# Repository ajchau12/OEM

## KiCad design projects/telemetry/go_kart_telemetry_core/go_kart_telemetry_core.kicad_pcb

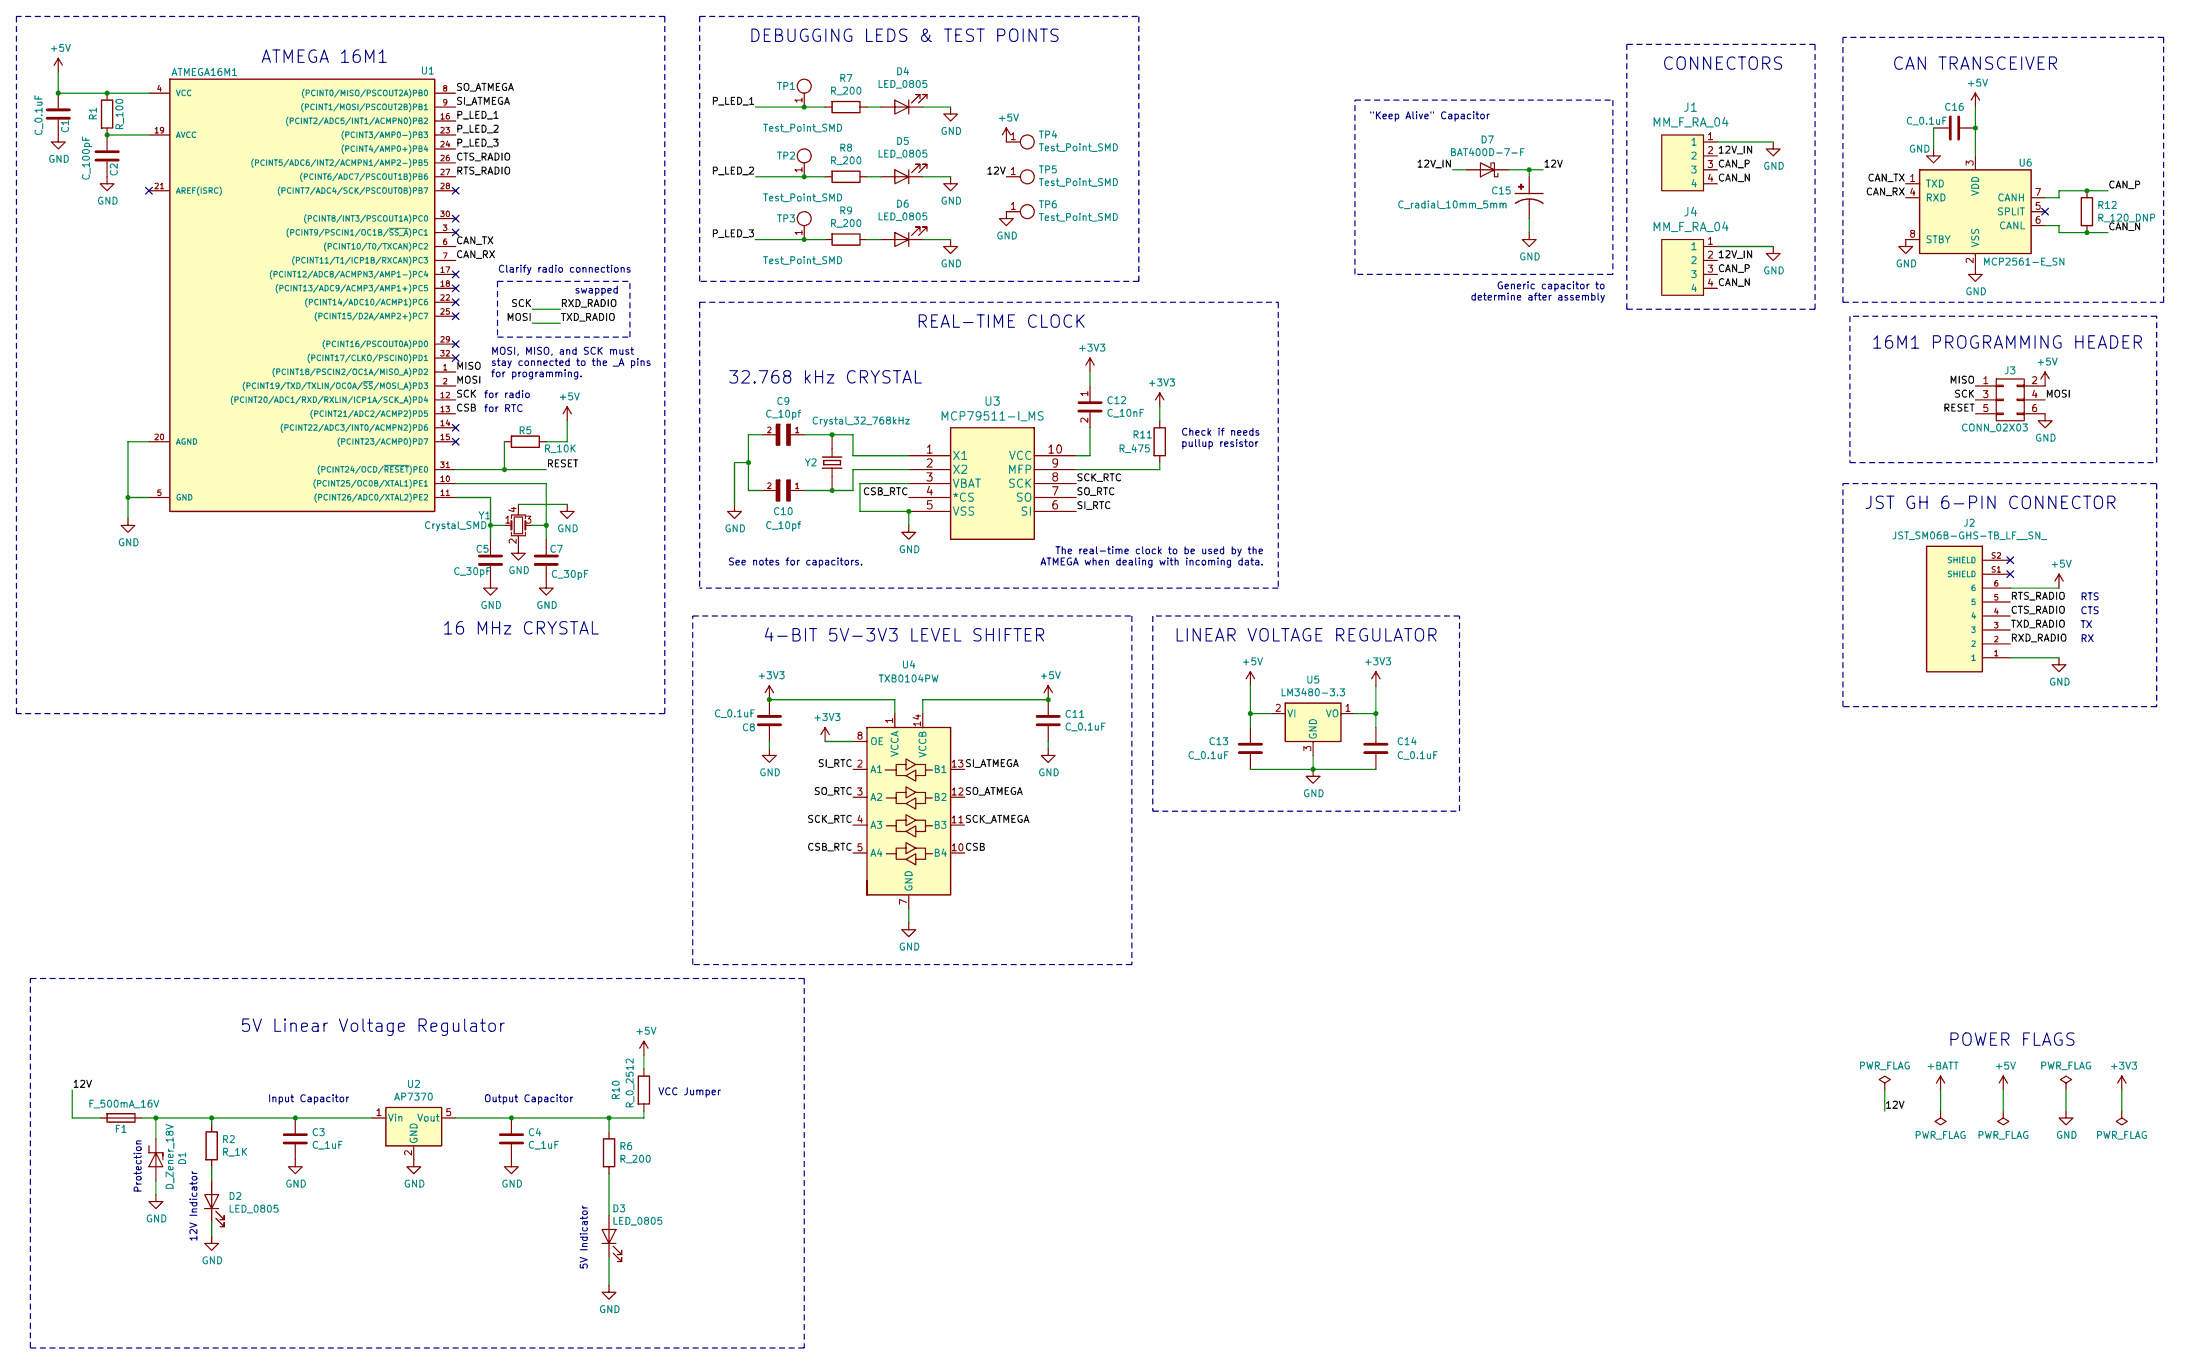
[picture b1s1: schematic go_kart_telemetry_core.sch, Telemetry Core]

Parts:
C1, C8, C11, C13, C14, C16: C_0.1uF; C_0805_OEM; MPN 478-3352-1-ND
C2: C_100pF; C_0805_OEM; MPN 732-7852-1-ND
C3, C4: C_1uF; C_0805_OEM
C5, C7: C_30pF; C_0805_OEM; MPN 1276-1130-1-ND
C9, C10: C_10pf
C12: C_10nF; C_1206_OEM; MPN C1206C103KCRACTU
C15: C_radial_10mm_5mm; PARTREV 28-FEB-20
D1: D_Zener_18V; DO-214AA; MPN SMBJ5355B-TPMSCT-ND
D2, D3, D4, D5, D6: LED_0805; LED_0805_OEM; MPN 475-1410-1-ND
D7: BAT400D-7-F; SOT-23-3_OEM
F1: F_500mA_16V; Fuse_1210; MPN 507-1786-1-ND
J1, J4: MM_F_RA_04; micromatch_female_ra_4; MPN 338070-4
J2: JST_SM06B-GHS-TB_LF__SN_; PARTREV N/A
J3: CONN_02X03; Pin_Header_Straight_2x03; MPN 609-3234-ND
R1: R_100; R_0805_OEM; MPN RNCP0805FTD100RCT-ND
R2: R_1K; R_0805_OEM; MPN RNCP0805FTD1K00CT-ND
R5: R_10K; R_0805_OEM; MPN CRS0805-FX-1002ELFCT-ND
R6, R7, R8, R9: R_200; R_0805_OEM; MPN RMCF0805JT200RCT-ND
R10: R_0_2512; R_2512_OEM; MPN A121322CT-ND
R11: R_475; R_0805_OEM; MPN 311-475CRCT-ND
R12: R_120_DNP; R_0805_OEM; MPN 667-ERJ-6ENF1200V
TP1, TP2, TP3, TP4, TP5, TP6: Test_Point_SMD
U1: ATMEGA16M1; TQFP-32_7x7mm_Pitch0.8mm; MPN ATMEGA16M1-AU-ND
U2: AP7370; SOT-23-5; MPN AP7370-50W5-7DICT-ND
U3: MCP79511-I_MS; MCP79511_I_MS
U4: TXB0104PW; TSSOP-14_4.4x5mm_P0.65mm
U5: LM3480-3.3; SOT-23
U6: MCP2561-E_SN; SOIC-8_3.9x4.9mm_Pitch1.27mm_OEM; MPN MCP2561-E/SN-ND
Y1: Crystal_SMD; Crystal_SMD_FA238; MPN 887-1125-1-ND
Y2: Crystal_32_768kHz; Crystal_32_768kHZ

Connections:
+3V3: C8.2, C12.1, C14.1, R11.1, U4.1 (VCCA), U4.8 (OE), U5.1 (VO)
+5V: C1.1, C11.1, C13.1, C16.1, J2.6, J3.2, R1.1, R5.1, R10.1, TP4.1, U1.4 (VCC), U4.14 (VCCB), U5.2 (VI), U6.3 (VDD)
/12V: C15.P, D7.1 (K), F1.2, TP5.1
/12V_IN: D7.2 (A), J1.2, J4.2
/CAN_N: J1.4, J4.4, R12.2, U6.6 (CANL)
/CAN_P: J1.3, J4.3, R12.1, U6.7 (CANH)
/CAN_RX: U1.7 ((PCINT11/T1/ICP1B/RXCAN)PC3), U6.4 (RXD)
/CAN_TX: U1.6 ((PCINT10/T0/TXCAN)PC2), U6.1 (TXD)
/CSB: U1.13 ((PCINT21/ADC2/ACMP2)PD5), U4.10 (B4)
/CSB_RTC: U3.4 (*CS), U4.5 (A4)
/CTS_RADIO: J2.4, U1.26 ((PCINT5/ADC6/INT2/ACMPN1/AMP2-)PB5)
/MISO: J3.1, U1.1 ((PCINT18/PSCIN2/OC1A/MISO_A)PD2)
/MOSI: J2.3, J3.4, U1.2 ((PCINT19/TXD/TXLIN/OC0A/~SS~/MOSI_A)PD3)
/P_LED_1: R7.2, TP1.1, U1.16 ((PCINT2/ADC5/INT1/ACMPN0)PB2)
/P_LED_2: R8.2, TP2.1, U1.23 ((PCINT3/AMP0-)PB3)
/P_LED_3: R9.2, TP3.1, U1.24 ((PCINT4/AMP0+)PB4)
/RESET: J3.5, R5.2, U1.31 ((PCINT24/OCD/~RESET~)PE0)
/RTS_RADIO: J2.5, U1.27 ((PCINT6/ADC7/PSCOUT1B)PB6)
/RXD_RADIO: J2.2, J3.3, U1.12 ((PCINT20/ADC1/RXD/RXLIN/ICP1A/SCK_A)PD4)
/SCK_ATMEGA: U4.11 (B3)
/SCK_RTC: U3.8 (SCK), U4.4 (A3)
/SI_ATMEGA: U1.9 ((PCINT1/MOSI/PSCOUT2B)PB1), U4.13 (B1)
/SI_RTC: U3.6 (SI), U4.2 (A1)
/SO_ATMEGA: U1.8 ((PCINT0/MISO/PSCOUT2A)PB0), U4.12 (B2)
/SO_RTC: U3.7 (SO), U4.3 (A2)
GND: C1.2, C2.2, C3.2, C4.2, C5.2, C7.2, C8.1, C9.2, C10.2, C11.2, C13.2, C14.2, C15.N, C16.2, D1.2 (A), D2.1 (K), D3.1 (K), D4.1 (K), D5.1 (K), D6.1 (K), J1.1, J2.1, J3.6, J4.1, TP6.1, U1.5 (GND), U1.20 (AGND), U2.2 (GND), U3.3 (VBAT), U3.5 (VSS), U4.7 (GND), U5.3 (GND), U6.2 (VSS), U6.8 (STBY), Y1.2, Y1.4
unnamed: C2.1, R1.2, U1.19 (AVCC)
unnamed: C3.1, D1.1 (K), F1.1, R2.1, U2.1 (Vin)
unnamed: C4.1, R6.1, R10.2, U2.5 (Vout)
unnamed: C5.1, U1.11 ((PCINT26/ADC0/XTAL2)PE2), Y1.1
unnamed: C7.1, U1.10 ((PCINT25/OC0B/XTAL1)PE1), Y1.3
unnamed: C9.1, U3.1 (X1), Y2.1
unnamed: C10.1, U3.2 (X2), Y2.2
unnamed: C12.2, U3.10 (VCC)
unnamed: D2.2 (A), R2.2
unnamed: D3.2 (A), R6.2
unnamed: D4.2 (A), R7.1
unnamed: D5.2 (A), R8.1
unnamed: D6.2 (A), R9.1
unnamed: R11.2, U3.9 (MFP)

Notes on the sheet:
12V Indicator
Protection
5V Linear Voltage Regulator
VCC Jumper
5V Indicator
CAN TRANSCEIVER
ATMEGA 16M1
16 MHz CRYSTAL
POWER FLAGS
16M1 PROGRAMMING HEADER
CONNECTORS
DEBUGGING LEDS & TEST POINTS
JST GH 6-PIN CONNECTOR
RTS
CTS
MOSI, MISO, and SCK must stay connected to the _A pins for programming.
LINEAR VOLTAGE REGULATOR
4-BIT 5V-3V3 LEVEL SHIFTER
REAL-TIME CLOCK
"Keep Alive" Capacitor
Clarify radio connections
Generic capacitor to determine after assembly
swapped
for RTC
Check if needs pullup resistor
for radio
See notes for capacitors.
The real-time clock to be used by the ATMEGA when dealing with incoming data.
32.768 kHz CRYSTAL
Input Capacitor
Output Capacitor

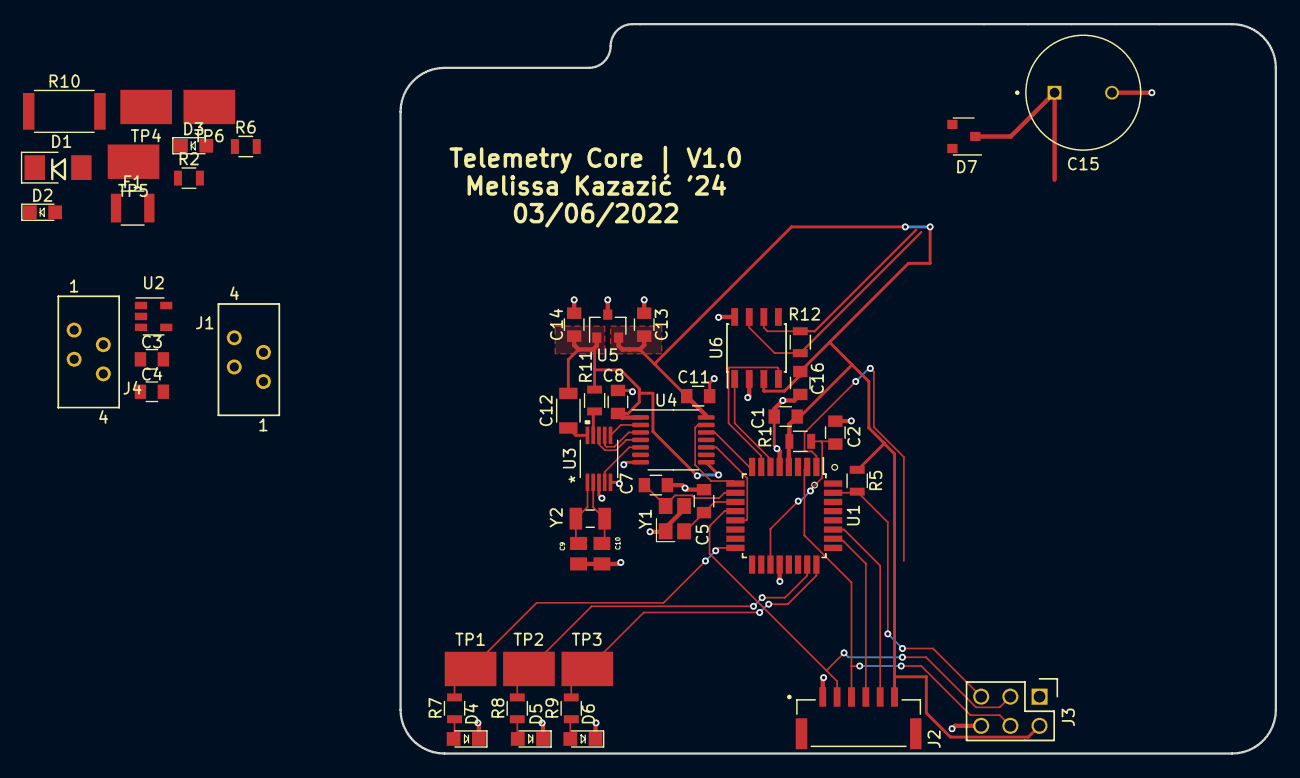
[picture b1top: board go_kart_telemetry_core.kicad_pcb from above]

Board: 2 copper layers, 76.2 x 63.5 mm, 51 parts (0 on the bottom side), 39 nets.

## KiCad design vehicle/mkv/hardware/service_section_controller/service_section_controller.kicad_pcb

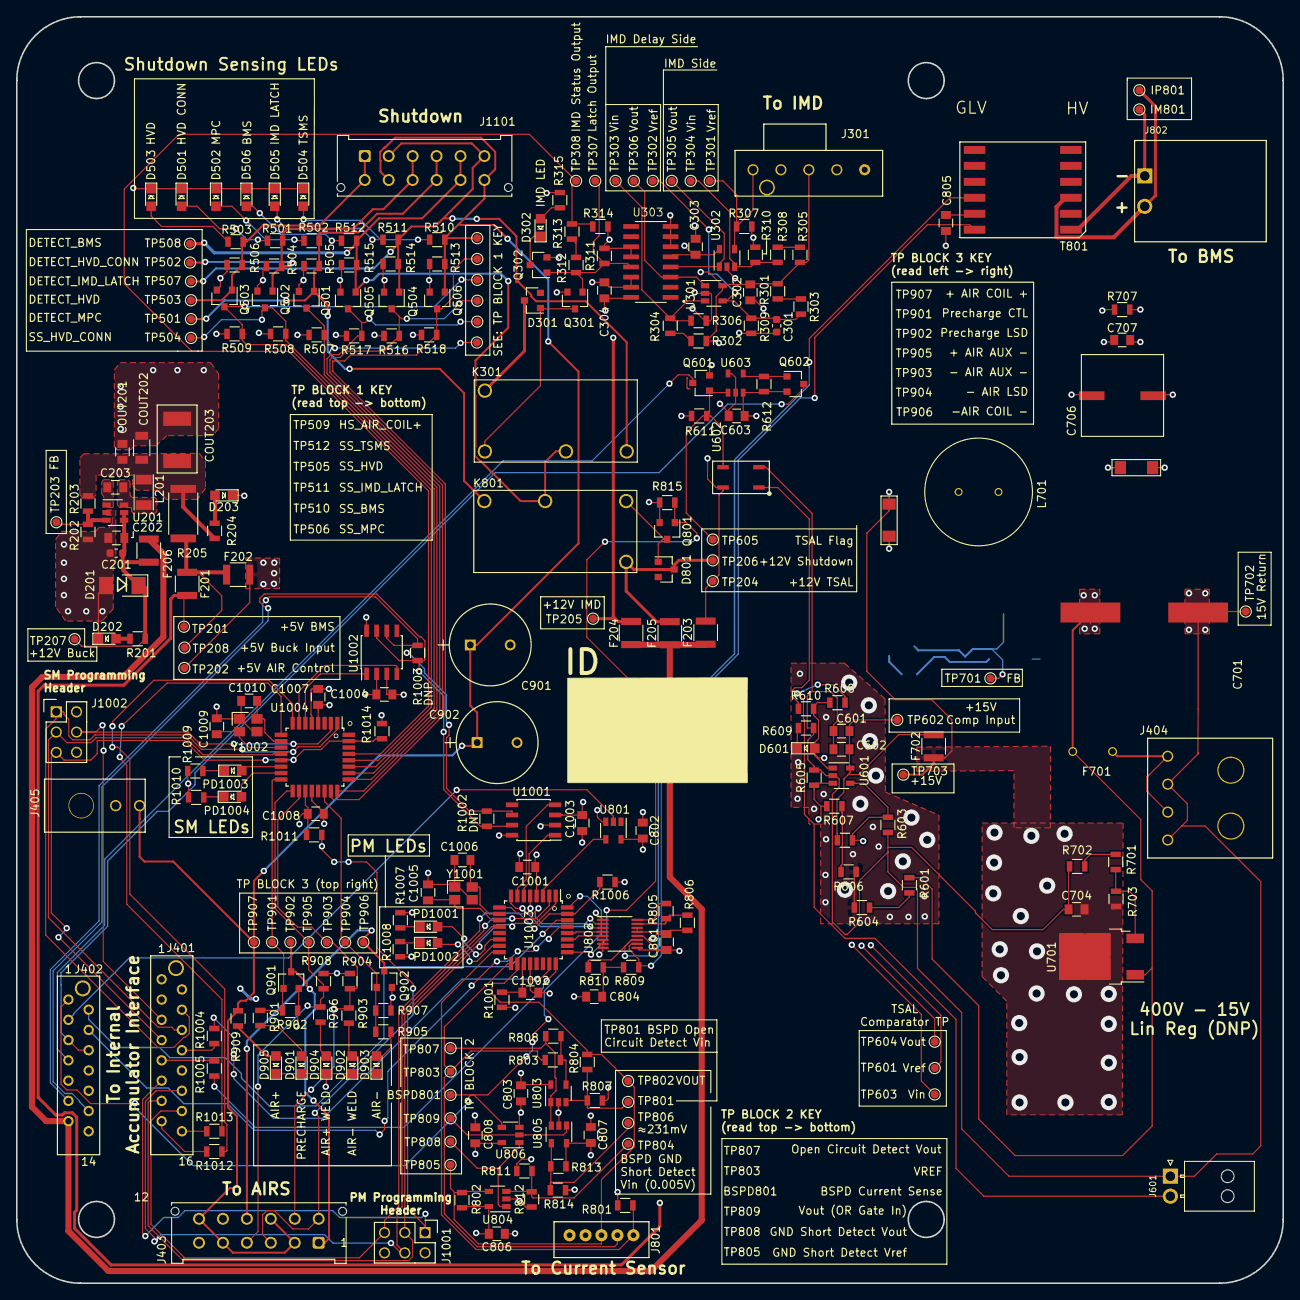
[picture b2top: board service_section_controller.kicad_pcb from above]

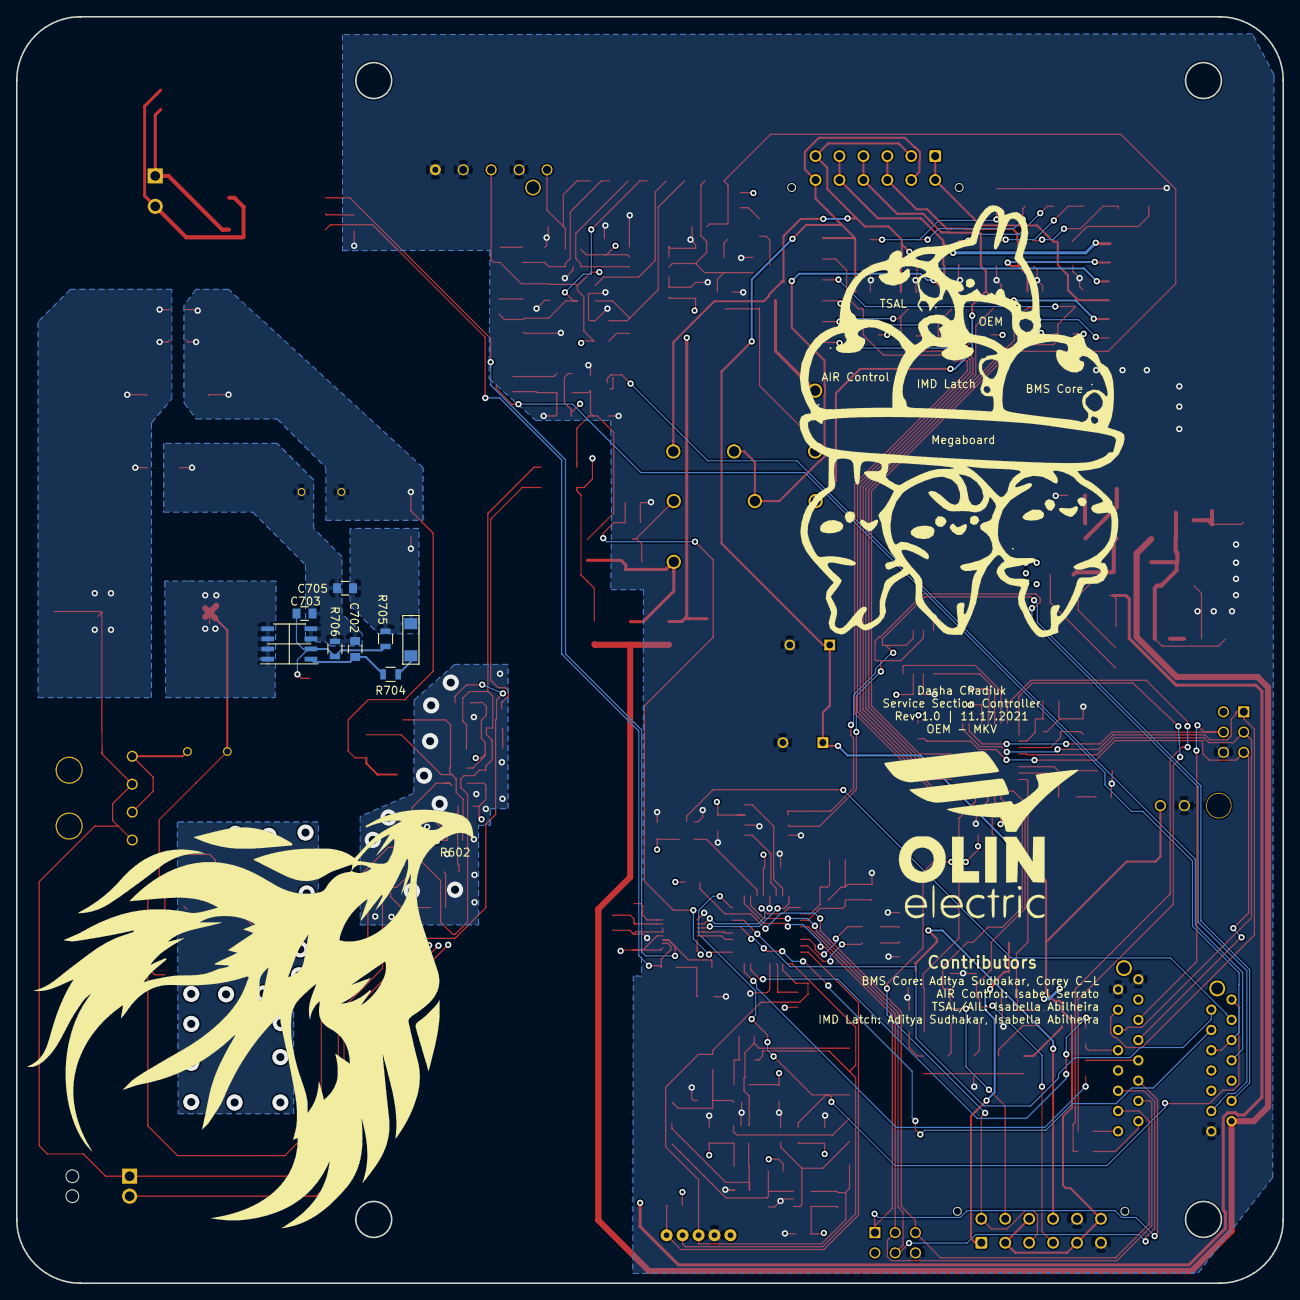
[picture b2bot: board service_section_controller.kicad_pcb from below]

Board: 4 copper layers, 158.8 x 158.8 mm, 274 parts (8 on the bottom side), 149 nets.

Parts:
BSPD801: Test_Point_SMD; TestPoint_Pad_D1.0mm
C201, C301: C_2.2uF; C_0603_1608Metric
C202, C203, C302, C303, C304, C602, C801, C802, C803, C806, C807, C808, C1001, C1003, C1004, C1007: C_0.1uF; C_0805_OEM
C601: C_10uF; C_0805_OEM
C603, C704, C707: C_1uF; C_0805_OEM
C701: C_10uF_450V
C702: C_2.2uF; C_0805_OEM
C703: C_470pF; C_0805_OEM
C705: C_.22uF; C_0805_OEM
C706: C_100uF+
C804, C805: C_10nF; C_0805_OEM
C901, C902: CP_1mF; C_Radial_D10_L13_P5_OEM
C1002, C1008: C_100pF; C_0805_OEM
C1005, C1006, C1009, C1010: C_30pF; C_0805_OEM
COUT201: C_47uF; C_0805_OEM
COUT202: C_22uF; C_1206_OEM
COUT203: C_33uF; Fuse_1812
D201: D_Zener_18V; DO-214AA
D202, D203, D302, D501, D502, D503, D504, D505, D506, D601, D901, D902, D903, D904, D905: LED_0805; LED_0805_OEM
D301, D801: BAS40-00; SOT-23
D701, D702, D703: Diode_600V_1A_SM
F201, F202, F203, F204, F205, F206, F702: 500mA; Fuse_1210
F701: F_21mA_420V
IM801: Test_Point_SMD; TestPoint_Pad_D1.0mm
IP801: Test_Point_SMD; TestPoint_Pad_D1.0mm
J301: UF_5_VT; Ultrafit_5
J401: MM_F_VT_16; micromatch_female_vert_16
J402: MM_F_VT_14; micromatch_female_vert_14
J403, J1101: MicroFit_VT_12
J404: Ultrafit_4_RA
J405: MicroFit_RA_V_2
J601: NanoFit_2; NanoFit_Molex_1x02x2.50mm_Angled_OEM
J801: B5B-PH-K-S
J802: isoSPI-Cutout; iso_spi_cutout
J1001, J1002: CONN_02X03; Pin_Header_Straight_2x03
K301, K801: G5Q-1A4-DC12; Relay_SPST_OMRON-G5Q-1A4_OEM
L201: L_100uH; L_100uH_OEM
L701: L_1.2mH
PD1001, PD1002, PD1003, PD1004: LED_0805; LED_0805_OEM
Q301, Q302, Q501, Q502, Q503, Q504, Q505, Q506, Q601, Q602, Q801, Q901, Q902: SSM3K333R; SOT-23F
R201, R301, R313, R315, R501, R502, R503, R510, R511, R512, R609, R805, R806, R812, R909: R_1K; R_0805_OEM
R202: R_25K; R_0805_OEM
R203, R504, R505, R506, R513, R514, R515: R_100K; R_0805_OEM
R204, R901, R903, R905, R906, R1004, R1005, R1007, R1008, R1009, R1010, R1012, R1013: R_200; R_0805_OEM
R205: R_0_2512; R_2512_OEM
R302, R305, R307, R312: R_2.2K; R_0805_OEM
R303: R_120K; R_0805_OEM
R304, R308: R_300K; R_0805_OEM
R306, R310, R311: R_604K; R_0805_OEM
R309: R_1.82M; R_0805_OEM
R314: R_1.13K; R_0805_OEM
R507, R508, R509, R516, R517, R518, R605, R611, R612, R704, R801, R802, R803, R804, R807, R808, R814, R815, R902, R904, R907, R908, R1006, R1014: R_10K; R_0805_OEM
R601, R604, R606, R607: R_270K; R_0805_OEM
R602: R_51.1K; R_0805_OEM
R603: R_1.91K; R_0805_OEM
R608: R_1.43K; R_0805_OEM
R610: R_499; R_0805_OEM
R701: R_43k; R_0805_OEM
R702, R705: R_23.7K; R_0805_OEM
R703: R_6.04K; R_0805_OEM
R706: R_4.99K; R_0805_OEM
R707: R_3K; R_0805_OEM
R809, R810: R_60.4; R_0805_OEM
R811: R_1M; R_0805_OEM
R813: R_475; R_0805_OEM
R1001, R1011: R_100; R_0805_OEM
R1002, R1003: R_120_DNP; R_0805_OEM
T801: T_LAN_SM91501ALE
TP201: 5V_BMS; TestPoint_Pad_D1.0mm
TP202: 5V_AIR_CONTROL; TestPoint_Pad_D1.0mm
TP203, TP701: FB; TestPoint_Pad_D1.0mm
TP204: 12V_TSAL; TestPoint_Pad_D1.0mm
TP205: 12V_IMD; TestPoint_Pad_D1.0mm
TP206: 12V_SHUTDOWN; TestPoint_Pad_D1.0mm
TP207: 12V_BUCK; TestPoint_Pad_D1.0mm
TP208: BUCK_OUTPUT; TestPoint_Pad_D1.0mm
TP301: IMD_OUTPUT; TestPoint_Pad_D1.0mm
TP302, TP303, TP306, TP307, TP801, TP804, TP805, TP806, TP807, TP808, TP809: Test_Point_SMD; TestPoint_Pad_D1.0mm
TP304: 8V_OPAMP; TestPoint_Pad_D1.0mm
TP305: OPAMP_OUTPUT; TestPoint_Pad_D1.0mm
TP308: IMD_STATUS_OUTPUT; TestPoint_Pad_D1.0mm
TP501: DETECT_MPC; TestPoint_Pad_D1.0mm
TP502: DETECT_HVD_CONN; TestPoint_Pad_D1.0mm
TP503: DETECT_HVD; TestPoint_Pad_D1.0mm
TP504: SS_HVD_CONN; TestPoint_Pad_D1.0mm
TP505: SS_HVD; TestPoint_Pad_D1.0mm
TP506: SS_MPC; TestPoint_Pad_D1.0mm
TP507: DETECT_IMD_LATCH; TestPoint_Pad_D1.0mm
TP508: DETECT_BMS; TestPoint_Pad_D1.0mm
TP509: DETECT_TSMS; TestPoint_Pad_D1.0mm
TP510: SS_BMS; TestPoint_Pad_D1.0mm
TP511: SS_IMD_LATCH; TestPoint_Pad_D1.0mm
TP512: SS_TSMS; TestPoint_Pad_D1.0mm
TP601: VIN; TestPoint_Pad_D1.0mm
TP602: 15V+; TestPoint_Pad_D1.0mm
TP603, TP803: VREF; TestPoint_Pad_D1.0mm
TP604: COMPARATOR_OUTPUT; TestPoint_Pad_D1.0mm
TP605: TSAL_FLAG; TestPoint_Pad_D1.0mm
TP702: 15V_RETURN; TestPoint_Pad_D1.0mm
TP703: 15V+_OUTPUT; TestPoint_Pad_D1.0mm
TP802: VOUT; TestPoint_Pad_D1.0mm
TP901: PRECHARGE_CTL; TestPoint_Pad_D1.0mm
TP902: PRECHARGE_LSD; TestPoint_Pad_D1.0mm
TP903: -AIR_WELD_DETECT; TestPoint_Pad_D1.0mm
TP904: -AIR_LSD; TestPoint_Pad_D1.0mm
TP905: +AIR_WELD_DETECT; TestPoint_Pad_D1.0mm
TP906: -AIR_COIL-; TestPoint_Pad_D1.0mm
TP907: +AIR_COIL+; TestPoint_Pad_D1.0mm
U201: TPS560430YF; SOT-23-6_OEM
U301, U302: TLV3701QDBVRG4Q1; SOT-23-5_OEM
U303: CD4044BDR; SOIC127P600X175-16N
U601: MCP6001; SOT-23-5
U602: CPC1025NTR; 4-pin_SOP
U603: BU4S11G2-TR; SSOP5
U701: LR8K4-G; TO-252-2
U702: MP9488; Converter_DCDC_MPS_MP9488
U801: SN74LVC1G17; SOT-23-5
U802: LTC6820HMS; MSOP-16_3x4mm_P0.5mm
U803, U804, U805: MCP6001; SOT-23-5_OEM
U806: SN74LVC1G32DBVR; SOT-23-5_OEM
U1001, U1002: MCP2561-E_SN; SOIC-8_3.9x4.9mm_Pitch1.27mm_OEM
U1003: ATMEGA64M1; TQFP-32_7x7mm_Pitch0.8mm
U1004: ATMEGA16M1; TQFP-32_7x7mm_Pitch0.8mm
Y1001, Y1002: Crystal_SMD; Crystal_SMD_FA238

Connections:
+5V: F201.1, F202.1, R205.1, TP208.1
+5V_AIR_CONTROL: C1004.1, C1007.1, F202.2, J401.10, J403.3, J403.7, J1002.2, R507.1, R508.1, R509.1, R516.1, R517.1, R518.1, R1011.1, R1014.1, TP202.1, U1002.3, U1004.4
+5V_BMS: C801.1, C802.2, C803.1, C806.1, C807.1, C808.1, C1001.1, C1003.1, F201.2, J401.3, J801.1, J1001.2, R801.1, R802.2, R811.1, R813.2, R1001.1, R1006.1, TP201.1, U801.5, U802.6, U802.7, U802.8, U802.9, U802.12, U803.5, U804.5, U805.5, U806.5, U1001.3, U1003.4
+12V_IMD: C302.2, C303.2, C304.2, F204.2, J301.3, R301.2, R302.2, R305.2, R315.1, TP205.1, U301.5, U302.5, U303.5, U303.16
+12V_SHUTDOWN: D301.3, D801.3, F205.2, K301.5, K801.5, TP206.1
+12V_TSAL: C603.2, F203.2, J402.8, J402.9, J402.10, TP204.1, U602.4, U603.2, U603.5
+15V: C704.1, C706.1, C707.1, D703.1, F702.1, L701.2, R703.1, R707.1, TP703.1, U701.2
+15V_FUSED: C601.2, C602.2, F702.2, R602.2, TP602.1, U601.5
+AIR_AUX-: J403.4, R906.1, R908.1, TP905.1, U1004.17
+AIR_COIL+: C901.1, C902.1, J403.2, J403.5, J403.9, J403.12, J405.2, J1101.8, J1101.12, Q506.1, R510.1, R513.1, R909.1, TP509.1, TP907.1
+AIR_COIL-: C201.2, C202.2, C301.2, C302.1, C303.1, C304.1, C603.1, C801.2, C802.1, C803.2, C804.2, C805.2, C806.2, C807.2, C808.2, C901.2, C902.2, C1001.2, C1002.2, C1003.2, C1004.2, C1005.2, C1006.2, C1007.2, C1008.2, C1009.2, C1010.2, COUT201.2, COUT202.2, COUT203.2, D201.2, D202.1, D203.1, D501.1, D502.1, D503.1, D504.1, D505.1, D506.1, D901.1, D902.1, D903.1, D904.1, D905.1, J301.2, J301.4, J301.5, J401.1, J401.2, J402.14, J403.6, J403.11, J405.1, J801.2, J1001.6, J1002.6, Q301.2, Q302.2, Q501.2, Q502.2, Q503.2, Q504.2, Q505.2, Q506.2, Q601.2, Q602.2, Q801.2, Q901.2, Q902.2, R202.2, R306.1, R307.2, R309.2, R310.1, R311.2, R314.2, R504.2, R505.2, R506.2, R513.2, R514.2, R515.2, R611.2, R612.2, R806.2, R807.1, R812.2, R814.1, R815.1, R902.2, R904.2, R907.2, R908.2, R1007.2, R1008.2, R1009.2, R1010.2, U201.2, U301.2, U302.2, U303.6, U303.7, U303.8, U303.11, U303.12, U303.14, U303.15, U603.3, U801.3, U802.1, U802.13, U802.14, U803.2, U804.2, U805.2, U806.3, U1001.2, U1001.8, U1002.2, U1002.8, U1003.5, U1003.20, U1004.5, U1004.20, Y1001.2, Y1001.4, Y1002.2, Y1002.4
+BATT: F203.1, F204.1, F205.1, F206.1, J402.13
+TS: F701.2, J404.1, J404.3
-AIR_AUX-: J403.8, R903.1, R904.1, TP903.1, U1004.18
-AIR_COIL-: J403.10, Q902.3, TP906.1
-AIR_LSD: Q902.1, R905.1, R907.1, TP904.1, U1004.22
-TS: C601.1, C602.1, C701.1, C704.2, C706.2, C707.2, D702.1, J404.2, J404.4, J601.1, R603.1, R605.2, R609.2, R702.2, R707.2, TP702.1, U601.2, U602.2
/imd_latch/LATCH_OUTPUT: Q301.1, Q302.1, R311.1, R312.1, TP307.1, U303.13
/micros/PM_DBG_1: PD1001.2, U1003.14
/micros/PM_DBG_2: PD1002.2, U1003.15
/micros/PM_RXCAN: U1001.4, U1003.7
/micros/PM_TXCAN: U1001.1, U1003.6
/micros/SM_DBG_1: PD1003.2, U1004.14
/micros/SM_DBG_2: PD1004.2, U1004.15
/micros/SM_RXCAN: U1002.4, U1004.7
/micros/SM_TXCAN: U1002.1, U1004.6
/power_main/+12V_BUCK: C201.1, C202.1, D201.1, F206.2, R201.1, TP207.1, U201.4, U201.5
/power_secondary.sch/FB: C703.1, R705.2, R706.1, TP701.1, U702.2
/power_secondary.sch/SW: C702.2, C703.2, C705.2, D702.2, L701.1, R706.2, U702.3, U702.4
/power_secondary.sch/VCC: C702.1, R704.2, U702.1
/tsal_ail/TSAL_FLAG: Q601.1, R611.1, TP605.1, U602.3, U603.1
AIL+: J601.2, R608.2
BMS_RELAY_DRIVE: Q801.1, R815.2, U1003.25
BSPD_CURRENT_SENSE: BSPD801.1, J402.1, U806.4, U1003.32
CANH: J402.12, R1002.1, R1003.1, U1001.7, U1002.7
CANL: J402.11, R1002.2, R1003.2, U1001.6, U1002.6
CHARGE_ENABLE1: J402.4, U1003.29
CHARGE_ENABLE2: J402.2, U1003.30
CS_ISO: U802.5, U1003.27
DETECT_BMS: J1101.5, J1101.11, K301.2, K801.2, Q505.1, R512.1, R515.1, TP508.1
DETECT_HVD: J1101.1, J1101.7, Q503.1, R503.1, R506.1, TP503.1
DETECT_HVD_CONN: J1101.3, J1101.9, Q502.1, R501.1, R504.1, TP502.1
DETECT_IMD_LATCH: J1101.2, J1101.6, K301.3, Q504.1, R511.1, R514.1, TP507.1
DETECT_MPC: J1101.4, J1101.10, K801.3, Q501.1, R502.1, R505.1, TP501.1
FAN_PWM: J402.3, U801.2
FAN_PWM_RAW: U801.4, U1003.3
IM: IM801.1, J802.1, T801.1
IMD_Output: J301.1, R307.1, TP301.1, U302.4
IMD_STATUS_OUTPUT: R313.2, R314.1, TP308.1, U1004.29
IP: IP801.1, J802.2, T801.3
MISO_ISO: U802.3, U1003.8
MOSI_ISO: U802.2, U1003.9
unnamed: C203.1, L201.1, U201.6
unnamed: C203.2, U201.1
unnamed: C301.1, R303.1, R309.1, TP302.1, U301.4
unnamed: C705.1, D701.1, D703.2, R705.1
unnamed: C804.1, R809.2, R810.1
unnamed: C805.1, T801.11
unnamed: C1002.1, R1001.2, U1003.19
unnamed: C1005.1, U1003.11, Y1001.1
unnamed: C1006.1, U1003.10, Y1001.3
unnamed: C1008.1, R1011.2, U1004.19
unnamed: C1009.1, U1004.11, Y1002.1
unnamed: C1010.1, U1004.10, Y1002.3
unnamed: COUT201.1, COUT202.1, COUT203.1, L201.2, R203.2, R204.1, R205.2
unnamed: D202.2, R201.2
unnamed: D203.2, R204.2
unnamed: D301.1, K301.1, Q301.3
unnamed: D302.1, Q302.3
unnamed: D302.2, R315.2
unnamed: D501.2, R501.2
unnamed: D502.2, R502.2
unnamed: D503.2, R503.2
unnamed: D504.2, R510.2
unnamed: D505.2, R511.2
unnamed: D506.2, R512.2
unnamed: D601.1, R609.1
unnamed: D601.2, R608.1, R610.2, TP604.1, U601.1
unnamed: D701.2, R704.1
unnamed: D801.1, K801.1, Q801.3
unnamed: D901.2, R901.2
unnamed: D902.2, R903.2
unnamed: D903.2, R905.2
unnamed: D904.2, R906.2
unnamed: D905.2, R909.2
unnamed: PD1001.1, R1007.1
unnamed: PD1002.1, R1008.1
unnamed: PD1003.1, R1009.1
unnamed: PD1004.1, R1010.1
unnamed: Q602.1, R612.1, U603.4
unnamed: R202.1, R203.1, TP203.1, U201.3
unnamed: R301.1, R303.2
unnamed: R302.1, R304.2
unnamed: R304.1, R306.2, TP303.1, U301.3
unnamed: R305.1, R308.2
unnamed: R308.1, R310.2, TP304.1, U302.3
unnamed: R312.2, R313.1
unnamed: R601.1, R604.2
unnamed: R602.1, R603.2, TP601.1, U601.4
unnamed: R604.1, R606.2
unnamed: R605.1, R607.1, TP603.1, U601.3
unnamed: R606.1, R607.2
unnamed: R610.1, U602.1
unnamed: R701.1, R703.2, U701.3
unnamed: R701.2, R702.1
unnamed: R803.2, R808.1, U803.4
unnamed: R804.2, R807.2, TP801.1, U803.3
unnamed: R805.1, U802.16
unnamed: R805.2, R806.1, U802.15
unnamed: R808.2, TP807.1, U803.1, U805.3
unnamed: R809.1, T801.12, U802.10
unnamed: R810.2, T801.10, U802.11
unnamed: R811.2, R812.1, TP804.1, U804.3
unnamed: R813.1, R814.2, TP806.1, U805.4
unnamed: R1004.2, U1003.23
unnamed: R1005.2, U1003.24
unnamed: R1012.2, U1004.8
unnamed: R1013.2, U1004.9
unnamed: TP305.1, U302.1, U303.4
unnamed: TP306.1, U301.1, U303.3
unnamed: TP808.1, U804.1, U806.1
unnamed: TP809.1, U805.1, U806.2
PM_MISO: J401.11, J1001.1, U1003.1
PM_MOSI: J401.12, J1001.4, U1003.2
PM_RESET: J401.14, J1001.5, R1006.2, U1003.31
PM_RJ45_LEDG: J401.8, R1004.1
PM_RJ45_LEDO: J401.9, R1005.1
PM_SCK: J401.13, J1001.3, U1003.12
PRECHARGE_CTL: Q901.1, R901.1, R902.1, TP901.1, U1004.16
PRECHARGE_LSD: J403.1, Q901.3, TP902.1
SCK_ISO: U802.4, U1003.28
SM_MISO: J401.4, J1002.1, U1004.1
SM_MOSI: J401.5, J1002.4, U1004.2
SM_RESET: J401.7, J1002.5, R1014.2, U1004.31
SM_RJ45_LEDG: J401.15, R1012.1
SM_RJ45_LEDO: J401.16, R1013.1
SM_SCK: J401.6, J1002.3, U1004.12
SS_BMS: Q505.3, R517.2, TP510.1, U1004.25
SS_HVD: Q503.3, R509.2, TP505.1, U1004.28
SS_HVD_CONN: Q502.3, R508.2, TP504.1, U1004.27
SS_IMD_LATCH: Q504.3, R516.2, TP511.1, U1004.24
SS_MPC: Q501.3, R507.2, TP506.1, U1004.26
SS_TSMS: Q506.3, R518.2, TP512.1, U1004.23
TS+_FUSED: C701.2, F701.1, R601.2, U701.1, U702.5, U702.6, U702.7, U702.8
TSAL_GREEN-: J402.5, J402.6, Q602.3
TSAL_RED-: J402.7, Q601.3
VOUT: J801.3, R802.1, R804.1, TP802.1, TP805.1, U804.4, U1003.18
VREF: J801.4, R803.1, TP803.1, U1003.17
nOCD: J801.5, R801.2, U1003.16

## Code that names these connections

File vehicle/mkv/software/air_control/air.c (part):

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}

void pcint0_callback(void) {
    air_control_critical.ss_tsms = !gpio_get_pin(SS_TSMS);
    air_control_critical.ss_imd = !gpio_get_pin(SS_IMD_LATCH);
    air_control_critical.ss_mpc = !gpio_get_pin(SS_MPC);
    air_control_critical.ss_hvd_conn = !gpio_get_pin(SS_HVD_CONN);
    air_control_critical.ss_hvd = !gpio_get_pin(SS_HVD);
}

void pcint1_callback(void) {
    air_control_critical.ss_bms = !gpio_get_pin(SS_BMS);
    air_control_critical.air_p_status = !!gpio_get_pin(AIR_P_WELD_DETECT);
    air_control_critical.air_n_status = !!gpio_get_pin(AIR_N_WELD_DETECT);
}
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        goto bail;
    }

    if (!gpio_get_pin(SS_TSMS)) {
        // SS_TSMS should start high
        air_control_critical.ss_tsms = true;
        set_fault(AIR_FAULT_SHUTDOWN_IMPLAUSIBILITY);
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        } break;
        case AIR_STATE_PRECHARGE: {
            // Start precharge
            gpio_set_pin(PRECHARGE_CTL);

            // Get pack voltage to compare with MC voltage
            int16_t pack_voltage = 0;
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                if (motor_controller_voltage
                    > (PRECHARGE_THRESHOLD * pack_voltage)) {
                    gpio_set_pin(AIR_N_LSD); // Close AIR_N
                    gpio_clear_pin(PRECHARGE_CTL); // Close precharge relay
                    once = true;
                    air_control_critical.air_state = AIR_STATE_TS_ACTIVE;
                    return;
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        } break;
        case AIR_STATE_FAULT: {
            gpio_set_pin(FAULT_LED);
            gpio_clear_pin(PRECHARGE_CTL);
            gpio_clear_pin(AIR_N_LSD);
        } break;
        default: {
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    timer_init(&timer0_cfg);
    timer_init(&timer1_cfg);

    gpio_set_mode(PRECHARGE_CTL, OUTPUT);
    gpio_set_mode(AIR_N_LSD, OUTPUT);
    gpio_set_mode(GENERAL_LED, OUTPUT);
    gpio_set_mode(FAULT_LED, OUTPUT);

    gpio_set_mode(IMD_SENSE, INPUT);
    gpio_set_mode(SS_TSMS, INPUT);
    gpio_set_mode(SS_IMD_LATCH, INPUT);
    gpio_set_mode(SS_BMS, INPUT);
    gpio_set_mode(SS_MPC, INPUT);
    gpio_set_mode(SS_HVD_CONN, INPUT);
    gpio_set_mode(SS_HVD, INPUT);

    gpio_enable_interrupt(SS_TSMS);
    gpio_enable_interrupt(SS_IMD_LATCH);
    gpio_enable_interrupt(SS_MPC);
    gpio_enable_interrupt(SS_HVD_CONN);
    gpio_enable_interrupt(SS_HVD);
    gpio_enable_interrupt(SS_BMS);
    gpio_enable_interrupt(IMD_SENSE);
    gpio_enable_interrupt(AIR_N_WELD_DETECT);
    gpio_enable_interrupt(AIR_P_WELD_DETECT);

    // Ensure pull-ups are disabled
    gpio_clear_pin(SS_TSMS);
    gpio_clear_pin(SS_IMD_LATCH);
    gpio_clear_pin(SS_MPC);
    gpio_clear_pin(SS_HVD_CONN);
    gpio_clear_pin(SS_HVD);

    air_control_critical.air_state = AIR_STATE_INIT;

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
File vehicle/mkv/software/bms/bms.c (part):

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 * Interrupt for nOCD
 */
void pcint0_callback(void) {
    bms_core.overcurrent_detect = !gpio_get_pin(nOCD);
}

/*
 * Interrupt for BSPD_CURRENT_SENSE
 */
void pcint2_callback(void) {
    bms_core.bspd_current_sense = !!gpio_get_pin(BSPD_CURRENT_SENSE);
}

/*
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
    int16_t current = 0;
    uint16_t vref = 0;
    uint16_t vout = 0;
    current_task(&current, &vref, &vout);
    bms_core.pack_current = current;
    bms_sense.current_vref = vref;
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        } break;
        case BMS_STATE_CHARGING: {
            gpio_set_pin(BMS_RELAY_LSD);
            gpio_set_pin(CHARGE_ENABLE1);
            gpio_set_pin(CHARGE_ENABLE2);

            if (ov > 0) {
                gpio_clear_pin(CHARGE_ENABLE1);
                gpio_clear_pin(CHARGE_ENABLE2);
                bms_core.bms_state = BMS_STATE_IDLE;
            }

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                can_receive_bms_charging();
                if (bms_charging.charge_enable == false) {
                    bms_core.bms_state = BMS_STATE_IDLE;
                    gpio_clear_pin(CHARGE_ENABLE1);
                    gpio_clear_pin(CHARGE_ENABLE2);
                }
            }
        } break;
        case BMS_STATE_FAULT: {
            gpio_clear_pin(CHARGE_ENABLE1);
            gpio_clear_pin(CHARGE_ENABLE2);
            gpio_clear_pin(BMS_RELAY_LSD);
            gpio_set_pin(FAULT_LED);

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    gpio_set_mode(BMS_RELAY_LSD, OUTPUT);
    gpio_set_mode(RJ45_LEDO, OUTPUT);
    gpio_set_mode(RJ45_LEDG, OUTPUT);
    gpio_set_mode(CHARGE_ENABLE1, OUTPUT);
    gpio_set_mode(CHARGE_ENABLE2, OUTPUT);
    gpio_set_mode(GENERAL_LED, OUTPUT);
    gpio_set_mode(FAULT_LED, OUTPUT);
    gpio_set_mode(FAN_PWM, OUTPUT);

    gpio_set_mode(nOCD, INPUT);
    gpio_set_mode(BSPD_CURRENT_SENSE, INPUT);

    gpio_set_pin(BMS_RELAY_LSD);

    gpio_enable_interrupt(nOCD);
    gpio_enable_interrupt(BSPD_CURRENT_SENSE);

    adc_init();

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
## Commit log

2022-02-14 Spi library and code samples
2022-02-14 Bazel-multi
2022-02-15 Add Serial Studio Documentation
    - Added JSON file that creates the visualizations
    - Added Arduino test file to show the visualizations with dummy serial
    code
    - Added a README for instructions on how to use Serial Studio
2022-02-24 added a microfit vertical 12-pos 2x6 3d model
2022-02-25 added 3d models for a 2-pos ra microfit, 14-pos vt micromatch, b5b-ph-k-s, and modified footprints library and service section controller to include the models
2022-03-07 fixed some connector 3d models on the service section controller
2022-03-08 fix: add missing connections, hide label
2022-03-08 fix MCP79511, start layout
2022-03-08 add 10pf and tht cap, update schematic
2022-03-08 fix: update schematic symbol ref for JST connector
2022-03-08 fix: change schematic symbol to be smaller and have background color
2022-03-08 add spi rtc meant for telemetry core board
2022-03-08 feat: connect rxd and txd for radio, big capacitor
2022-03-08 feat: set up schematic for rtc and add crystal
2022-03-08 feat: begin layout process
2022-03-08 fix: small changes to schematic symbol
2022-03-08 Add Telemetry Core incl. debugging leds, test points, 20-pin connector
2022-03-08 feat: near-complete layout
2022-03-08 feat: spec out caps for rtc, ATMEGA connects
2022-03-08 fix: Rename kicad hardware to telemetry core
2022-03-08 feat: begin changes from mk5 schematic
2022-03-08 feat: add JST-GH 6-pin Connector to library
2022-03-08 fix: add copper zone
2022-03-08 fix: Rename telemetry core directory to all lowercase
2022-03-08 feat: complete v1 layout
2022-03-08 add: 32.768Hz Crystal
2022-03-08 fix: rename 3D model file to no parentheses
2022-03-08 fix: rename symbol and footprint for JST connector
2022-03-08 branch from mk5 board, rename folder
2022-03-09 feat: begin changes for gokart
2022-04-17 Start docker converstion
2022-05-18 Integrate shared memory library
2022-05-18 Add flash library
2022-05-18 Add UART library
    Also adds example to blinky
2022-05-18 Add image library
2022-05-18 Add crc32 library
2022-05-18 clang-format
2022-05-18 Add more comments and fix APIs
2022-05-18 --wip-- [skip ci]
2022-05-18 buildify
2022-05-18 Initial CAN Software Update Client code
2022-05-18 Clang-format and fix unused
2022-05-18 Add a bunch of files
2022-05-18 Add initial bootloader client code
2022-05-18 Integrate Bazel into bootloader
2022-05-18 buildifier
2022-05-18 clang_format
2022-05-18 Add ability to flash bootloader and patch header
2022-05-18 Fix build issues with patched binary
2022-05-18 Fix client integration with Bazel
2022-05-18 More fixes including runfiles issue
    --wip-- [skip ci]
2022-05-18 Replace jump instruction
2022-05-18 Fix issues in building
2022-05-18 Format
2022-05-18 Fix bugs
2022-05-18 Add SeeedStudio CAN bridge
2022-05-18 Fix last page not getting written issue
2022-05-18 Resolve AIR control conflicts
2022-05-18 Reorganize
2022-05-18 Black
2022-05-18 Revert library changes
2022-05-18 Fix build issue for non-btldr-enabled images
2022-05-18 Whoops, minor bug in last commit
2022-05-18 Remove 64m1 support from AIR control until it is supported in BTLDR
2022-05-18 Clean up process for adding btldr to images
2022-05-18 Add btldr to dashboard
2022-05-18 Fix btldr in dashboard and add to throttle
2022-05-18 Add btldr to BSPD (and rename)
2022-05-18 Add btldr to bms
2022-05-18 Clean up
2022-05-18 Clean up CAN IDs
2022-05-18 Fix default BTLDR ID issue
2022-05-18 Fix CAN masks to check 3 bits instead of 4
2022-07-20 Add blinky0
2022-07-20 Add bare ADC
2022-07-21 Add blinky plus tutorial
2022-07-21 Add numbers for ADC enum
2022-07-28 Fix volatile bug
2022-07-28 Add fake-motor-controller command yml
2022-08-03 Add enum generation to CAN API
2022-08-16 created folders within mkvi folder for hardware, bms, and peripheral
2022-08-28 Add ADBMS1818 and new 3D model folder to parts library
2022-09-12 Update 29-bit CAN ID support
2022-09-12 Refactor BMS state machine
2022-09-12 Initial structure for CHARGING state in AIR control
2022-09-12 Add charging support to AIR controller
2022-09-12 Add 29/11-bit ID toggle
2022-09-12 Add charging support to BMS and simplify state machine
2022-09-12 Add charging library
2022-09-12 Update charging code for AIR control
2022-09-12 Integrate charging firmware
2022-09-12 Charging
2022-09-12 Remove charging CAN code
2022-09-12 Fix air control yml
2022-09-12 Fix issue with ltc chip timeout and wakeup
2022-09-18 Split schematic into sheets
2022-09-20 Switch FTPROG to button and update I2C level shifter
